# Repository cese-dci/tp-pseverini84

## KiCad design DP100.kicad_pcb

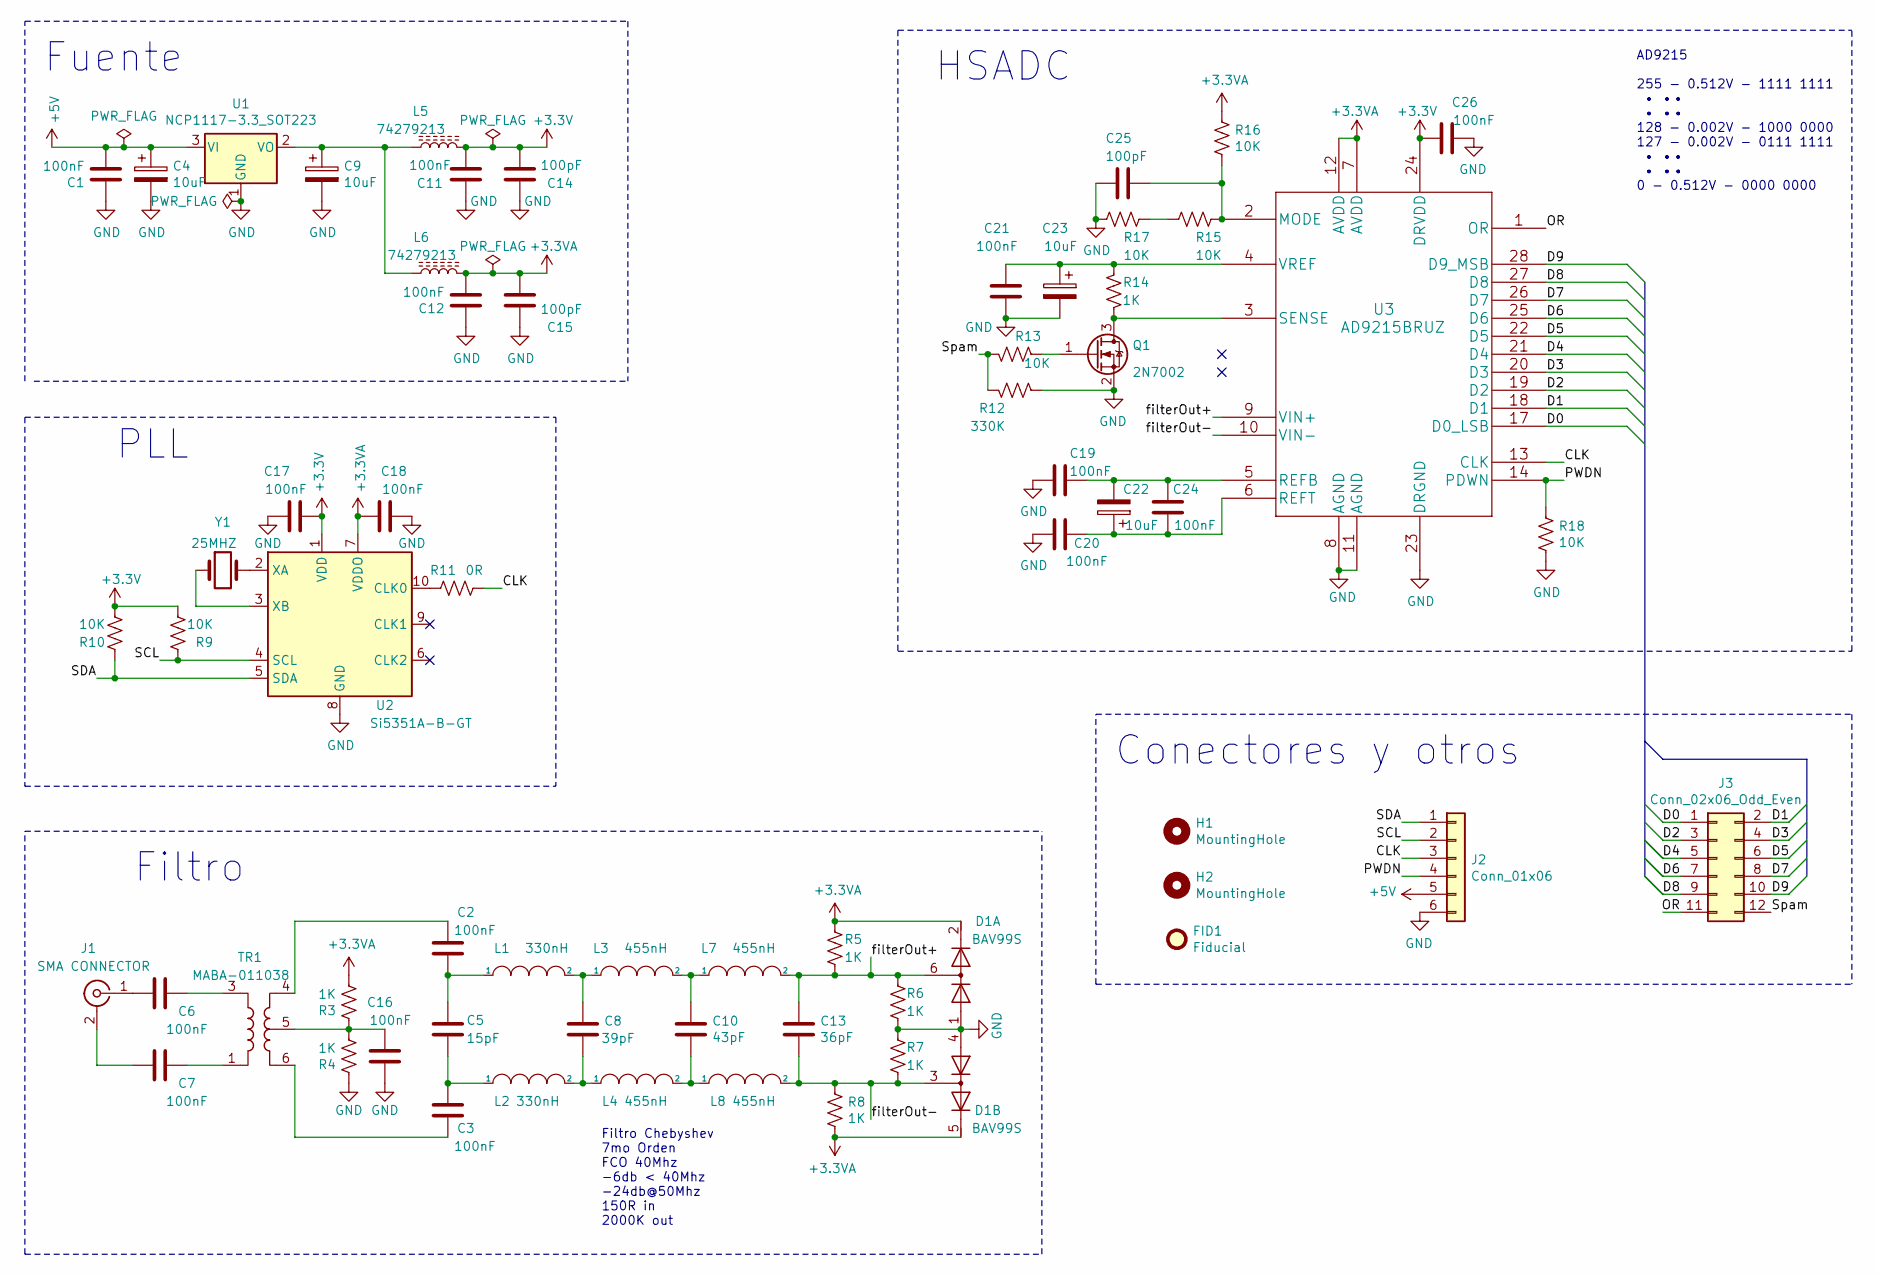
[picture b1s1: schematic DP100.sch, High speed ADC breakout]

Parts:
C1, C2, C3, C6, C7, C11, C12, C16, C17, C18, C19, C20, C21, C24, C26: 100nF; C_0603_1608Metric_Pad1.05x0.95mm_HandSolder; Mouser 80-C0603C104Z3V
C4, C9, C22, C23: 10uF; CP_EIA-2012-15_AVX-P_Pad1.30x1.05mm_HandSolder; Mouser 647-F920J106MPA
C5: 15pF; C_0603_1608Metric_Pad1.05x0.95mm_HandSolder; Mouser 710-885012006033
C8: 39pF; C_0603_1608Metric_Pad1.05x0.95mm_HandSolder; Mouser 80-C0603C390J5GAC
C10: 43pF; C_0603_1608Metric_Pad1.05x0.95mm_HandSolder; Mouser 603-CC603JRNPO9BN430
C13: 36pF; C_0603_1608Metric_Pad1.05x0.95mm_HandSolder; Mouser 603-CC603JRNPO9BN360
C14, C15, C25: 100pF; C_0603_1608Metric_Pad1.05x0.95mm_HandSolder; Mouser 80-C0603C101K1HACTU
D1: BAV99S; SOT-363_SC-70-6; Mouser 771-BAV99S-T/R
FID1: Fiducial; Fiducial_0.5mm_Mask1mm
H1, H2: MountingHole; MountingHole_3mm
J1: SMA CONNECTOR; SMA_Amphenol_901-144_Vertical; Mouser 471-SMARACONNECTOR
J2: Conn_01x06; PinHeader_1x06_P2.54mm_Vertical; Mouser 855-M20-9754046
J3: Conn_02x06_Odd_Even; PinHeader_2x06_P2.54mm_Vertical; Mouser 855-M20-9760642
L1, L2: 330nH; L_1206_3216Metric_Pad1.42x1.75mm_HandSolder; Mouser 963-LBM2016TR33JV
L3, L4, L7, L8: 455nH; L_0805_2012Metric_Pad1.15x1.40mm_HandSolder; Mouser 963-BRC1608TR45M
L5, L6: 74279213; C_1206_3216Metric_Pad1.42x1.75mm_HandSolder; Mouser 710-74279213
Q1: 2N7002; SOT-23; Mouser 512-2N7002
R3, R4, R5, R6, R7, R8, R14: 1K; R_0603_1608Metric_Pad1.05x0.95mm_HandSolder; Mouser 71-CRCW06031K00FKEAC
R9, R10, R13, R15, R16, R17, R18: 10K; R_0603_1608Metric_Pad1.05x0.95mm_HandSolder; Mouser 71-CRCW0603-10K-E3
R11: 0R; R_0603_1608Metric_Pad1.05x0.95mm_HandSolder; Mouser 603-AC0603JR-130RL
R12: 330K; R_0603_1608Metric_Pad1.05x0.95mm_HandSolder; Mouser 603-RC0603FR-07330KL
TR1: MABA-011038; Mini-Circuits_DB1627; Mouser 937-MABA-011038
U1: NCP1117-3.3_SOT223; SOT-223-3_TabPin2; Mouser 863-NCP1117ST33T3G
U2: Si5351A-B-GT; MSOP-10_3x3mm_P0.5mm; Mouser 634-SI5351A-B-GTR
U3: AD9215BRUZ; TSSOP-28_4.4x9.7mm_P0.65mm; Mouser 584-AD9215BRUZ-105
Y1: 25MHZ; Crystal_SMD_ECS_CSM3X-2Pin_7.6x4.1mm; Mouser 815-ABLS7M225MHZD2YT

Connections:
+3.3VA: C12.2, C15.2, C18.1, D1.2 (K2), D1.5 (K4), L6.2, R3.2, R5.1, R8.2, R16.1, U2.7 (VDDO), U3.7 (AVDD), U3.12 (AVDD)
+3V3: C11.1, C14.2, C17.1, C26.2, L5.1, R9.2, R10.2, U2.1 (VDD), U3.24 (DRVDD)
+5V: C1.2, C4.1, J2.5, U1.3 (VI)
/CLK: J2.3, R11.2, U3.13 (CLK)
/D0: J3.1, U3.17 (D0_LSB)
/D1: J3.2, U3.18 (D1)
/D2: J3.3, U3.19 (D2)
/D3: J3.4, U3.20 (D3)
/D4: J3.5, U3.21 (D4)
/D5: J3.6, U3.22 (D5)
/D6: J3.7, U3.25 (D6)
/D7: J3.8, U3.26 (D7)
/D8: J3.9, U3.27 (D8)
/D9: J3.10, U3.28 (D9_MSB)
/OR: J3.11, U3.1 (OR)
/PWDN: J2.4, R18.1, U3.14 (PDWN)
/SCL: J2.2, R9.1, U2.4 (SCL)
/SDA: J2.1, R10.1, U2.5 (SDA)
/Spam: J3.12, R12.1, R13.1
/filterOut+: C13.1, D1.6 (K3A4), L7.2, R5.2, R6.2, U3.9 (VIN+)
/filterOut-: C13.2, D1.3 (K1A2), L8.2, R7.1, R8.1, U3.10 (VIN-)
GND: C1.1, C4.2, C9.2, C11.2, C12.1, C14.1, C15.1, C16.1, C17.2, C18.2, C19.2, C20.2, C21.2, C23.2, C25.2, C26.1, D1.1 (A1), D1.4 (A3), J2.6, Q1.2 (S), R4.1, R6.1, R7.2, R12.2, R17.2, R18.2, U1.1 (GND), U2.8 (GND), U3.8 (AGND), U3.11 (AGND), U3.23 (DRGND)
unnamed: C2.1, C5.1, L1.1
unnamed: C2.2, TR1.4
unnamed: C3.1, C5.2, L2.1
unnamed: C3.2, TR1.6
unnamed: C6.1, TR1.3
unnamed: C6.2, J1.1 (In)
unnamed: C7.1, TR1.1
unnamed: C7.2, J1.2 (Ext)
unnamed: C8.1, L1.2, L3.1
unnamed: C8.2, L2.2, L4.1
unnamed: C9.1, L5.2, L6.1, U1.2 (VO)
unnamed: C10.1, L3.2, L7.1
unnamed: C10.2, L4.2, L8.1
unnamed: C16.2, R3.1, R4.2, TR1.5
unnamed: C19.1, C22.2, C24.1, U3.5 (REFB)
unnamed: C20.1, C22.1, C24.2, U3.6 (REFT)
unnamed: C21.1, C23.1, R14.1, U3.4 (VREF)
unnamed: C25.1, R15.1, R16.2, U3.2 (MODE)
unnamed: Q1.1 (G), R13.2
unnamed: Q1.3 (D), R14.2, U3.3 (SENSE)
unnamed: R11.1, U2.10 (CLK0)
unnamed: R15.2, R17.1
unnamed: U2.2 (XA), Y1.2
unnamed: U2.3 (XB), Y1.1

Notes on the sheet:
Fuente
Conectores y otros
AD9215 255 - 0.512V - 1111 1111 • •• • •• 128 - 0.002V - 1000 0000 127 - 0.002V - 0111 1111 • •• • •• 0 - 0.512V - 0000 0000
HSADC
Filtro
PLL
Filtro Chebyshev 7mo Orden FCO 40Mhz -6db < 40Mhz -24db@50Mhz 150R in 2000K out

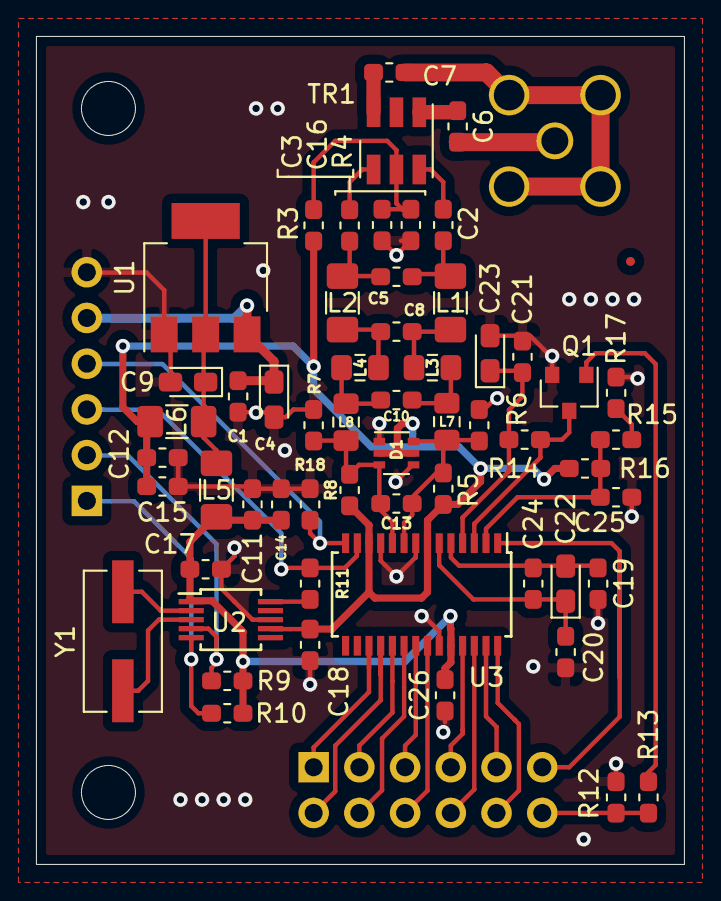
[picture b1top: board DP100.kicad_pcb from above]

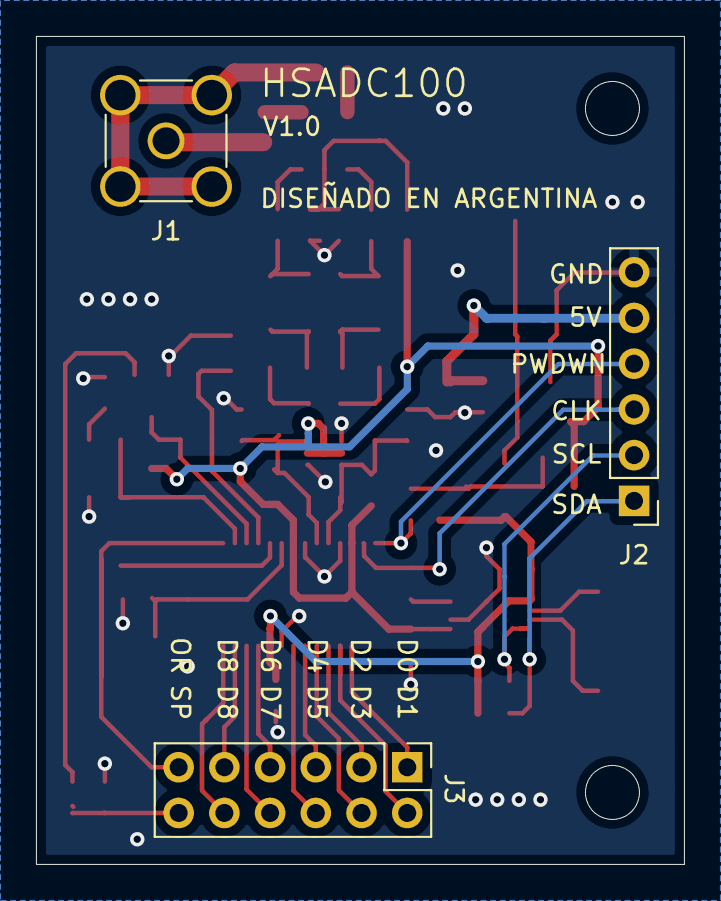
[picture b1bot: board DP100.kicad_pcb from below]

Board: 2 copper layers, 36.0 x 46.0 mm, 63 parts (3 on the bottom side), 46 nets.

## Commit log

2021-04-02 Se agrega esquematico para primera revision
2021-04-03 Correcciones realizadas sobre el esquematico a partir de la revision realizada el dia 2/4 por Francisco Timez
2021-04-03 Cambio de etiquetas globales por jerarquicas en el esquematico. Posicionamiento de componentes y ruteo de PCB
2021-04-03 Mascara de componentes posicionada correctamente Planos de tierra en ambas caras Reglas chequeadas segun fabricante Ernesto Mayer
2021-04-07 Se cambian las etiquetas jerarquicas por net labels.
2021-04-08 Se agregan cotas
2021-04-09 Se agregan modelos 3d faltantes
2021-04-10 Se agregan correcciones realizadas por Francisco Timez el dia 10-4 -Fiduciarios -Serigrafias faltantes -Otro agujero de sujecion
2021-04-12 Correcciones en base a devolucion de Diego Brengi del dia 12-4-2021 -Se expanden las zonas compactas -Se agrega directorio con informacion extra -Se agregan lineas para evitar que los labels toquen d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
2021-04-13 Se agrega rotulo en el pcb
2021-04-13 Se agregan notas en PCB
2021-04-20 Se realizan correcciones sugeridas el dia 20-4 -se agregan models 3d -se corrigen las notas -se modifican los planos de tierra segun sugerencia -se remueven serigrafias que se encontraban sobre vias 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

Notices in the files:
DP100.kicad_pcb:
Released under the Creative Commons Attribution Share-Alike 4.0 Licence
DP100.sch:
https://creativecommons.org/license/by-sa/4.0
